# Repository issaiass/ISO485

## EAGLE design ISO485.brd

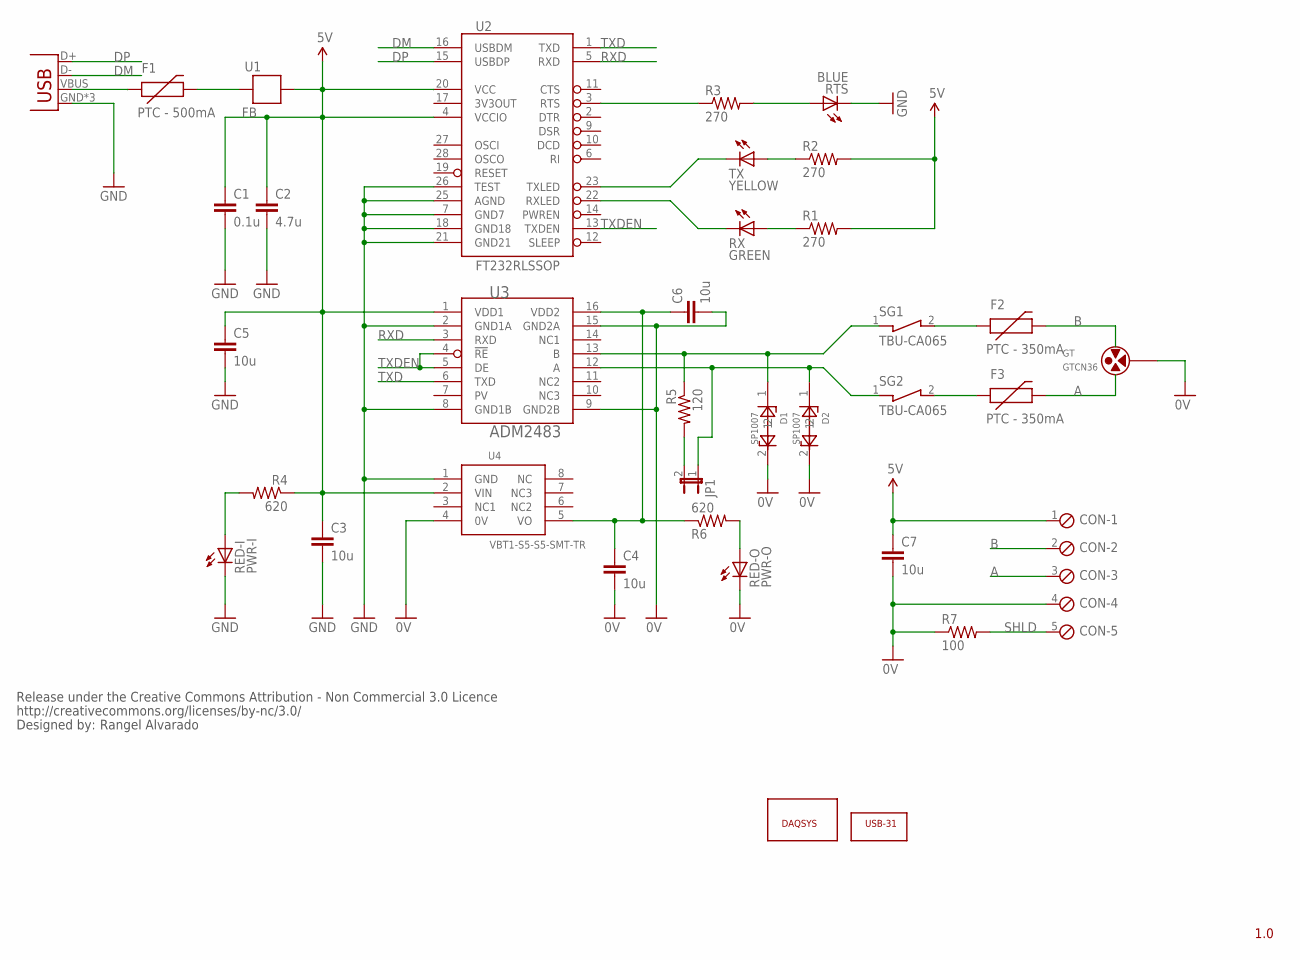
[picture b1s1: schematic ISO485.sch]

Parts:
C1: 0.1u; 0603-CAP
C2: 4.7u; 0603-CAP
C3, C4, C5, C6, C7: 10u; 0603-CAP
CON: MPT5; 5POL254
D1, D2: SP1007; 0603
F1: PTC - 500mA; 0603
F2, F3: PTC - 350mA; 0603
GT: GTCN36; SMT-GDT
JP1: JUMPER-2PTH; 1X02
R1, R2, R3: 270; 0402-RES
R4, R6: 620; 0402-RES
R5: 120; 0402-RES
R7: 100; 1206
RED-I: PWR-I; LED-1206
RED-O: PWR-O; LED-1206
RTS: BLUE; LED-0603
RX: GREEN; LED-0603
SG1, SG2: TBU-CA065; SMD
TX: YELLOW; LED-0603
U1: FB; 0603
U2: FT232RLSSOP; SSOP28DB
U3: ADM2483; SOIC-16
U4: VBT1-S5-S5-SMT-TR; SMD-8
U$1: CC-BY-NC
U$2: DAQSYS
U$3: USB-31; USB-PCB-RECT
USB: USB-MICROB

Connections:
0V: C4.2, C6.2, C7.2, CON.4, D1.2, D2.2, GT.3, R7.1, RED-O.C, U3.9 (GND2B), U3.15 (GND2A), U4.4 (0V)
5V: C1.1, C2.1, C3.1, C5.1, C7.1, CON.1, R1.2, R2.2, R4.1, U1.1, U2.4 (VCCIO), U2.20 (VCC), U3.1 (VDD1), U4.2 (VIN)
A: CON.3, F3.2, GT.2
B: CON.2, F2.2, GT.1
DM: U2.16 (USBDM), USB.D-
DP: U2.15 (USBDP), USB.D+
GND: C1.2, C2.2, C3.2, C5.2, RED-I.C, RTS.C, U2.7 (GND7), U2.18 (GND18), U2.21 (GND21), U2.25 (AGND), U2.26 (TEST), U3.2 (GND1A), U3.8 (GND1B), U4.1 (GND), USB.GND, USB.MT1 (GND), USB.MT2 (GND)
unnamed: F1.1, USB.VBUS
unnamed: F1.2, U1.2
unnamed: R4.2, RED-I.A
unnamed: TX.C, U2.23 (TXLED)
unnamed: RX.C, U2.22 (RXLED)
unnamed: R2.1, TX.A
unnamed: R1.1, RX.A
unnamed: R3.1, U2.3 (RTS)
unnamed: R3.2, RTS.A
unnamed: D1.1, R5.1, SG1.1, U3.13 (B)
unnamed: C4.1, C6.1, R6.1, U3.16 (VDD2), U4.5 (VO)
unnamed: D2.1, JP1.1, SG2.1, U3.12 (A)
unnamed: F2.1, SG1.2
unnamed: F3.1, SG2.2
unnamed: JP1.2, R5.2
unnamed: R6.2, RED-O.A
RXD: U2.5 (RXD), U3.3 (RXD)
SHLD: CON.5, R7.2
TXD: U2.1 (TXD), U3.6 (TXD)
TXDEN: U2.13 (TXDEN), U3.4 (!RE), U3.5 (DE)

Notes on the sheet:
1.0
Rangel Alvarado

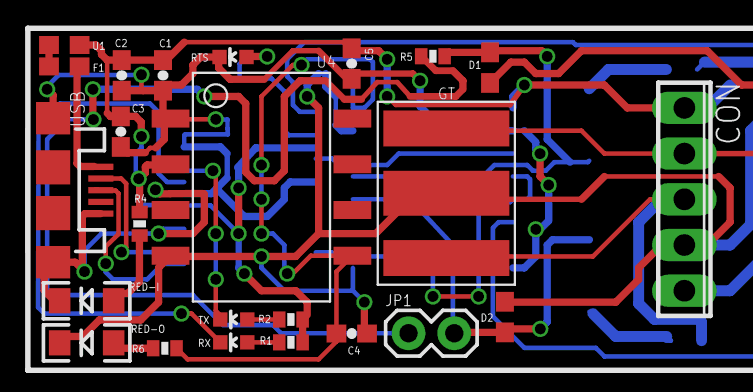
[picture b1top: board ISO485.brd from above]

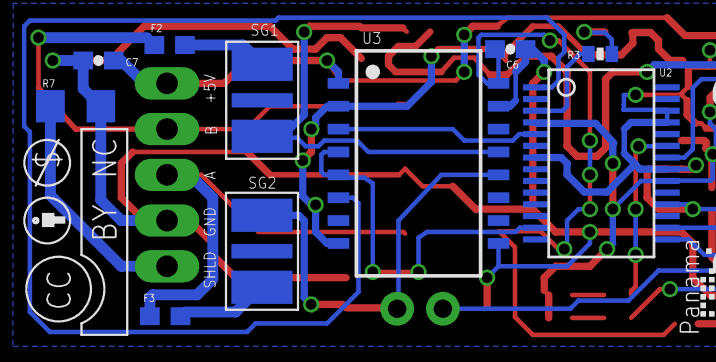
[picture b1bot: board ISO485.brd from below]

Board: 2 copper layers, 37 parts (12 on the bottom side), 27 nets.

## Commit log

2014-11-01 :boom::camel: Added .gitattributes & .gitignore files
2014-11-01 Isolated USB to RS-485 board
    Galvanic isolated board from USB 2.0 to RS-485

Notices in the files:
parts and their libraries:
SparkFun-Connectors: Licensing: CC v3.0 Share-Alike You are welcome to use this library for commercial purposes.
ISO485: Release under the Creative Commons Attribution - Non Commercial 3.0 Licence
ISO485: http://creativecommons.org/licenses/by-nc/3.0
